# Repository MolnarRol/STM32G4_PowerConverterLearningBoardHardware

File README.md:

# STM32F4_PowerConverterLearningBoardHardware

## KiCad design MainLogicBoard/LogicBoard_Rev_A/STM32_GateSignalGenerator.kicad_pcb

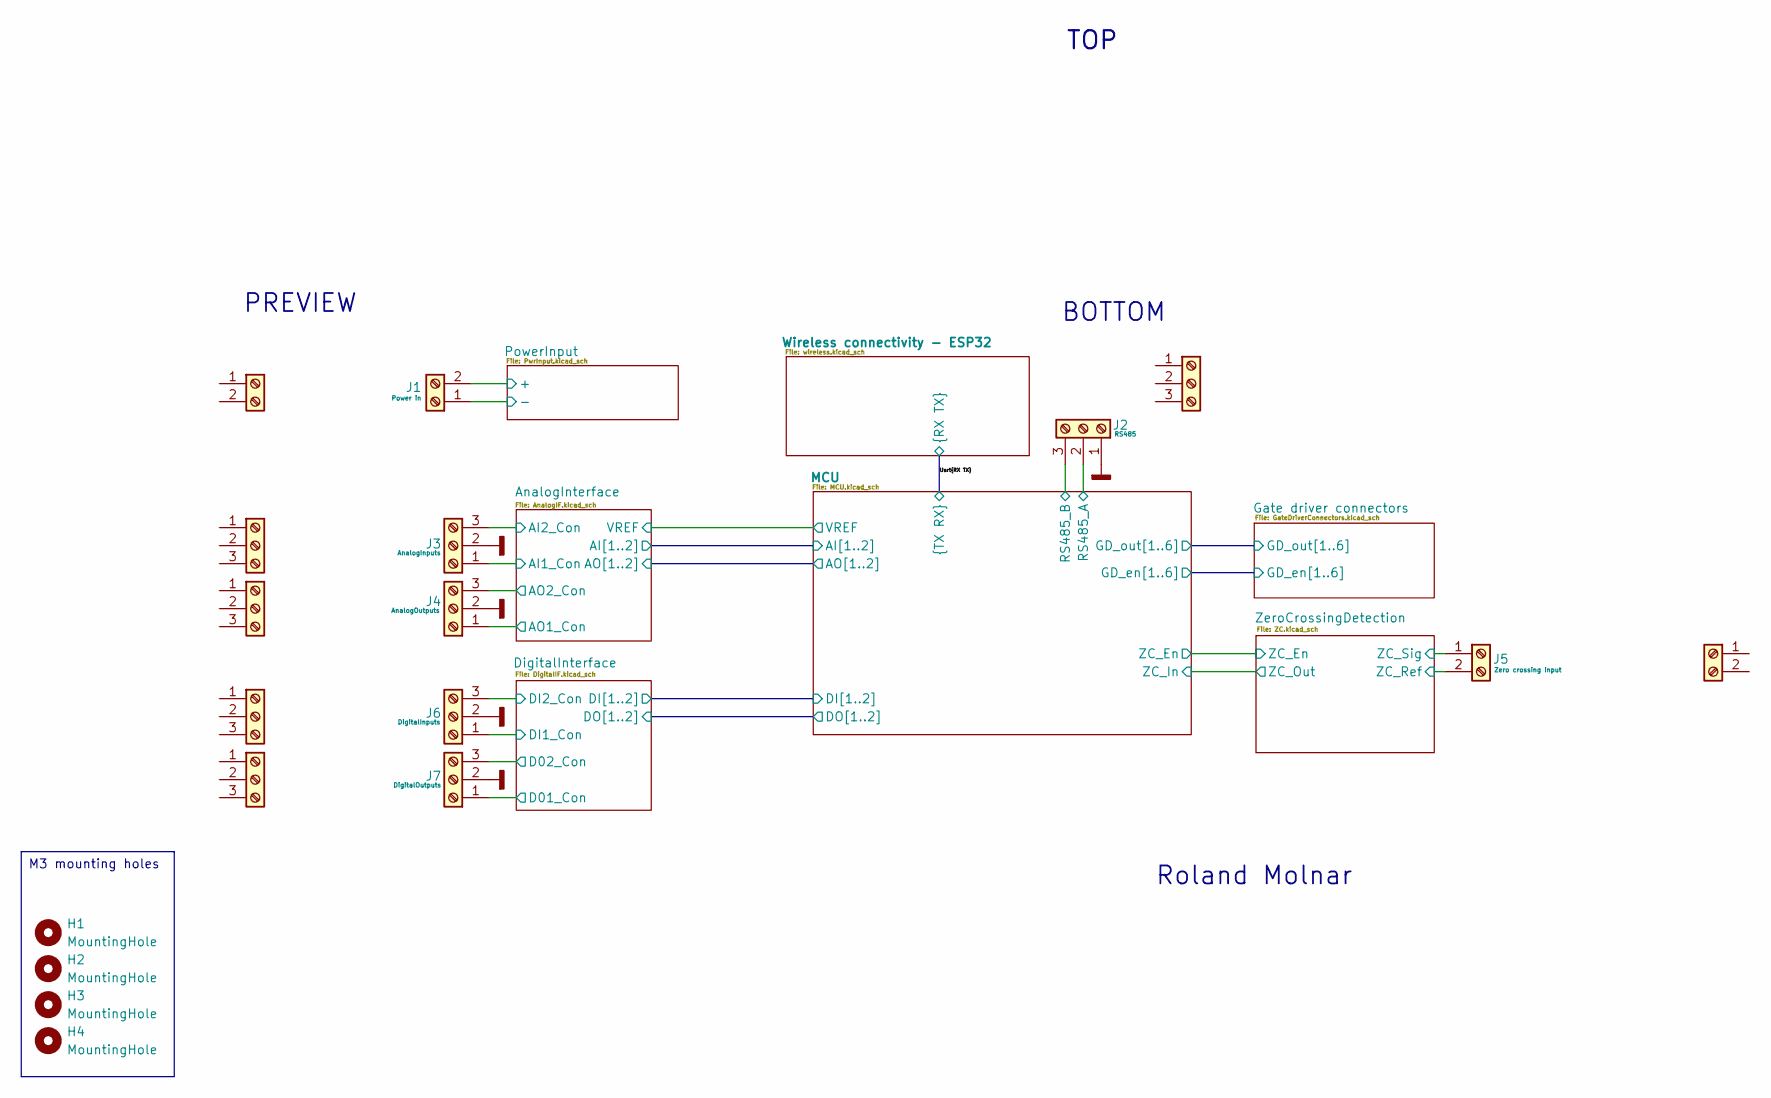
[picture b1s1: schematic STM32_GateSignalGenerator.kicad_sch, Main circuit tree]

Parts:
H1, H2, H3, H4: MountingHole; MountingHole_3.2mm_M3
J1: Power in; TE 2350514-2; Manufacturer PN 2350514-2; DigiKey PN A145378-ND
J2: RS485; TE 2350514-3; Manufacturer PN 2350514-3; DigiKey PN A145379-ND
J3: AnalogInputs; TE 2350514-3; Manufacturer PN 2350514-3; DigiKey PN A145379-ND
J4: AnalogOutputs; TE 2350514-3; Manufacturer PN 2350514-3; DigiKey PN A145379-ND
J5: Zero crossing input; PhoenixContact_MSTBA_2,5_2-G-5,08_1x02_P5.08mm_Horizontal; Manufacturer PN 1757242; DigiKey PN 277-1106-ND
J6: DigitalInputs; TE 2350514-3; Manufacturer PN 2350514-3; DigiKey PN A145379-ND
J7: DigitalOutputs; TE 2350514-3; Manufacturer PN 2350514-3; DigiKey PN A145379-ND
J22: Screw_Terminal_01x02; Manufacturer PN 2350398-2; DigiKey PN A145367-ND
J23, J24, J25, J26, J27: Screw_Terminal_01x03; Manufacturer PN 284506-3; DigiKey PN A98374-ND
J28: Screw_Terminal_01x02; Manufacturer PN 1757019; DigiKey PN 277-1011-ND

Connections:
/AnalogInterface/AI1_Con: J3.1; also elsewhere on the board
/AnalogInterface/AI2_Con: J3.3; also elsewhere on the board
/AnalogInterface/AO1_Con: J4.1; also elsewhere on the board
/AnalogInterface/AO2_Con: J4.3; also elsewhere on the board
/DigitalInterface/D01_Con: J7.1; also elsewhere on the board
/DigitalInterface/D02_Con: J7.3; also elsewhere on the board
/DigitalInterface/DI1_Con: J6.1; also elsewhere on the board
/DigitalInterface/DI2_Con: J6.3; also elsewhere on the board
/MCU/rs485_a: J2.2; also elsewhere on the board
/MCU/rs485_b: J2.3; also elsewhere on the board
/PowerInput/PWR_IN_+24V: J1.2; also elsewhere on the board
/ZeroCrossingDetection/ZC_Ref: J5.2; also elsewhere on the board
/ZeroCrossingDetection/ZC_Sig: J5.1; also elsewhere on the board
GNDD: J1.1, J2.1, J3.2, J4.2, J6.2, J7.2; also elsewhere on the board

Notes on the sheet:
PREVIEW
Roland Molnar
BOTTOM
TOP
M3 mounting holes

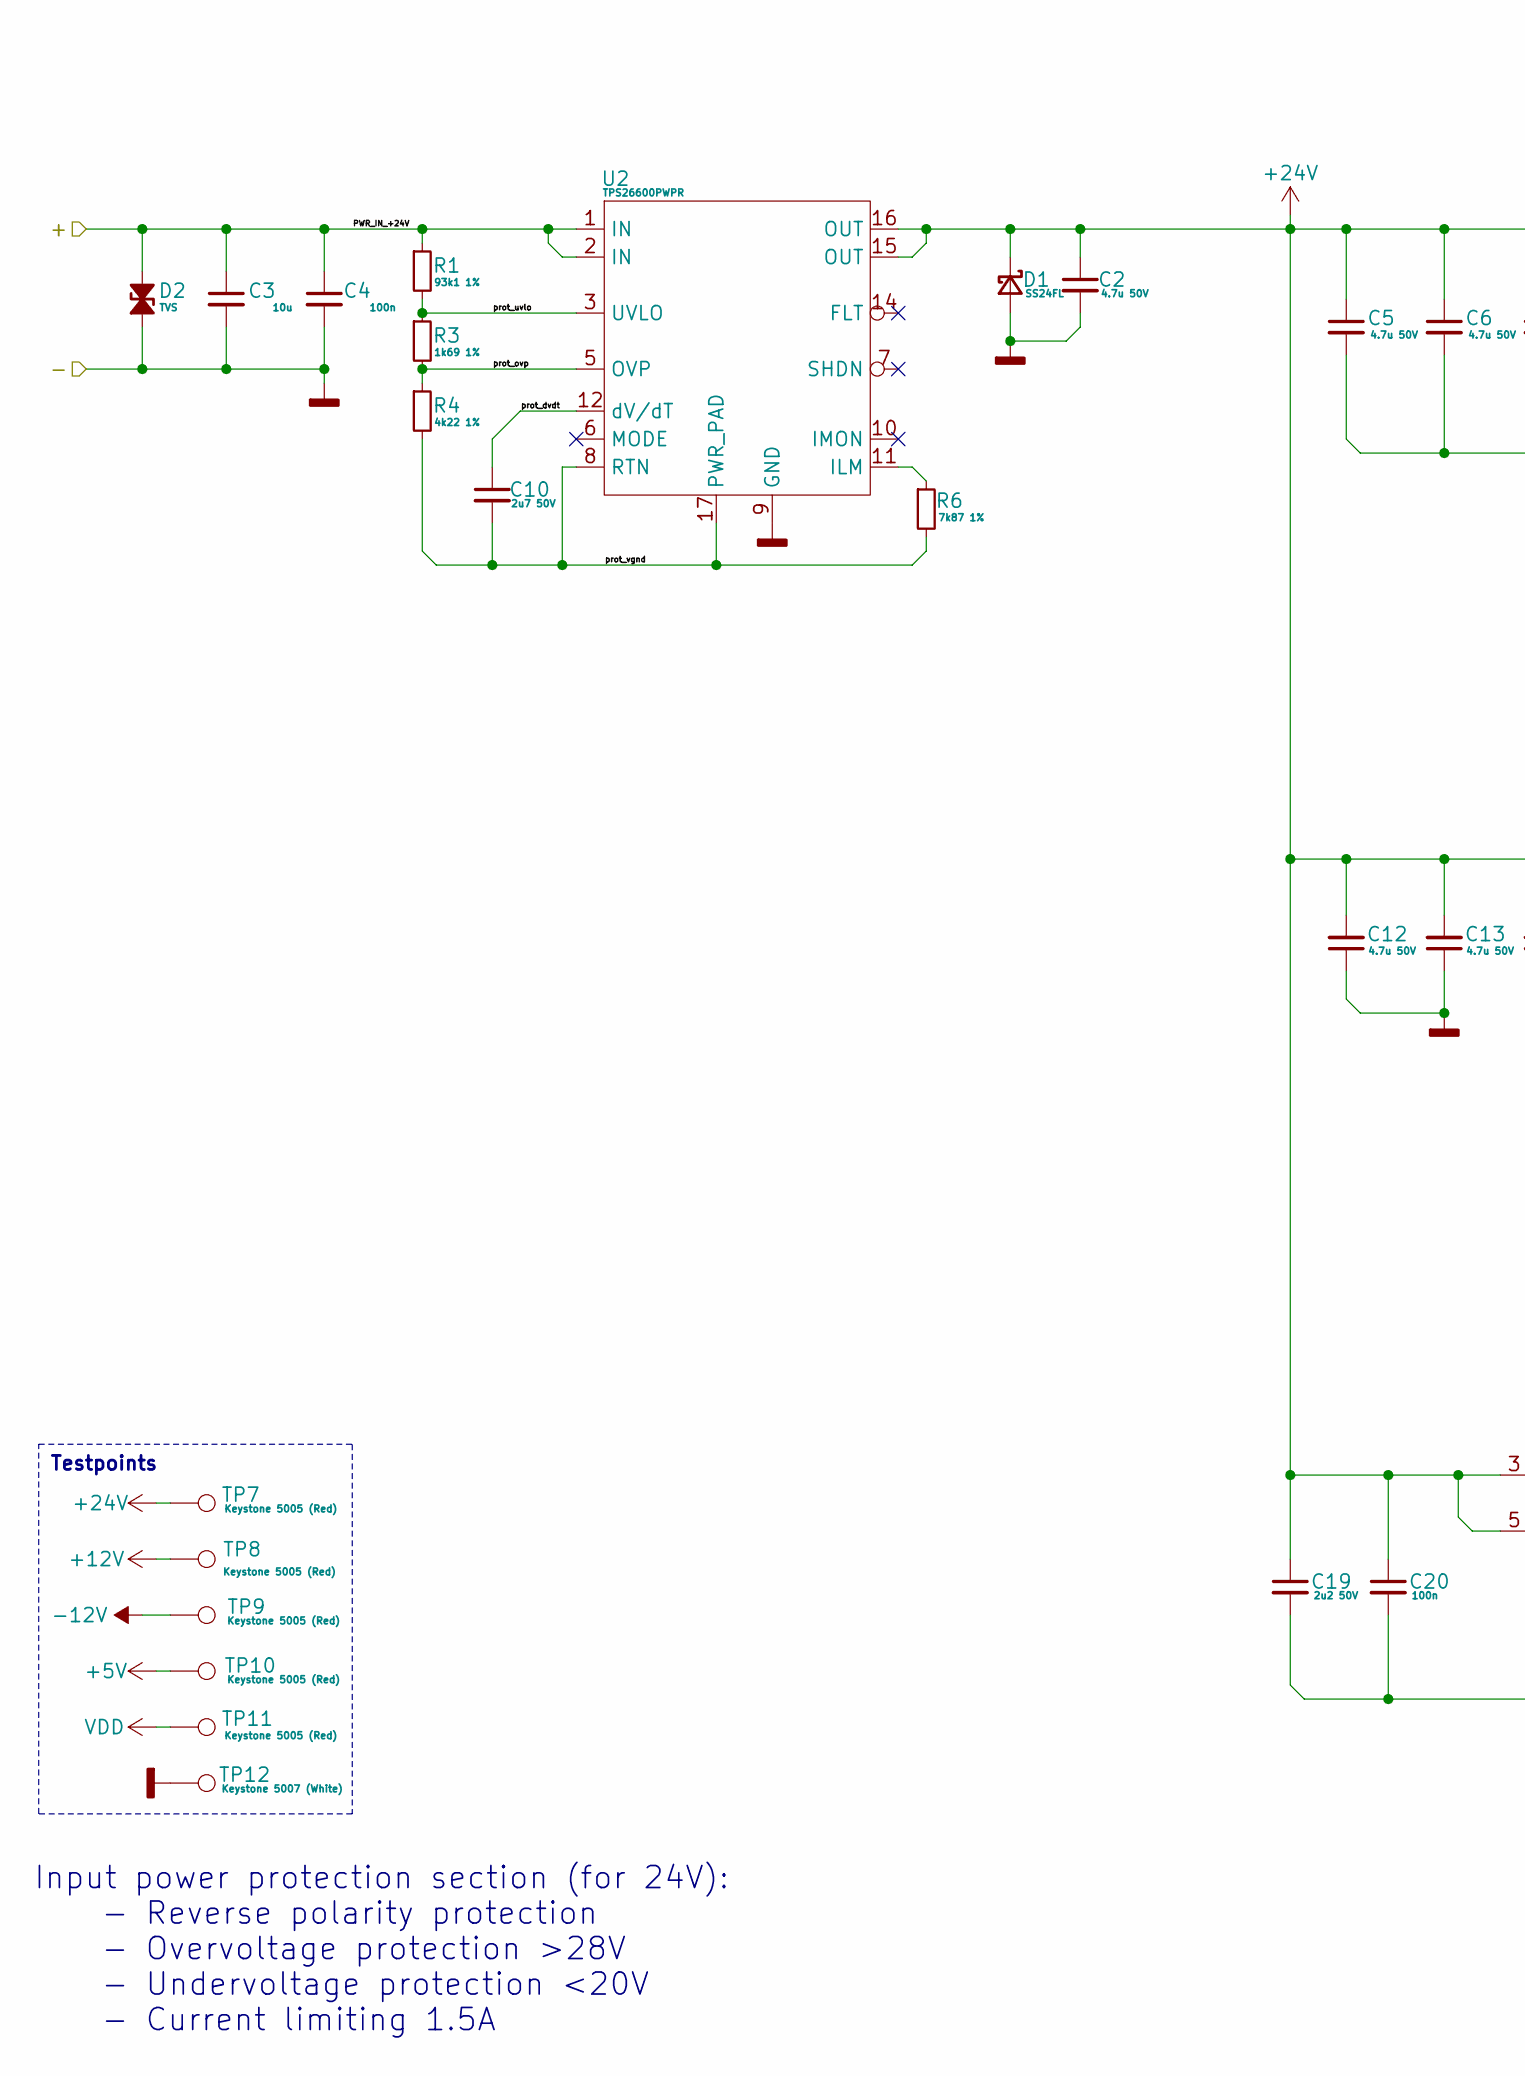
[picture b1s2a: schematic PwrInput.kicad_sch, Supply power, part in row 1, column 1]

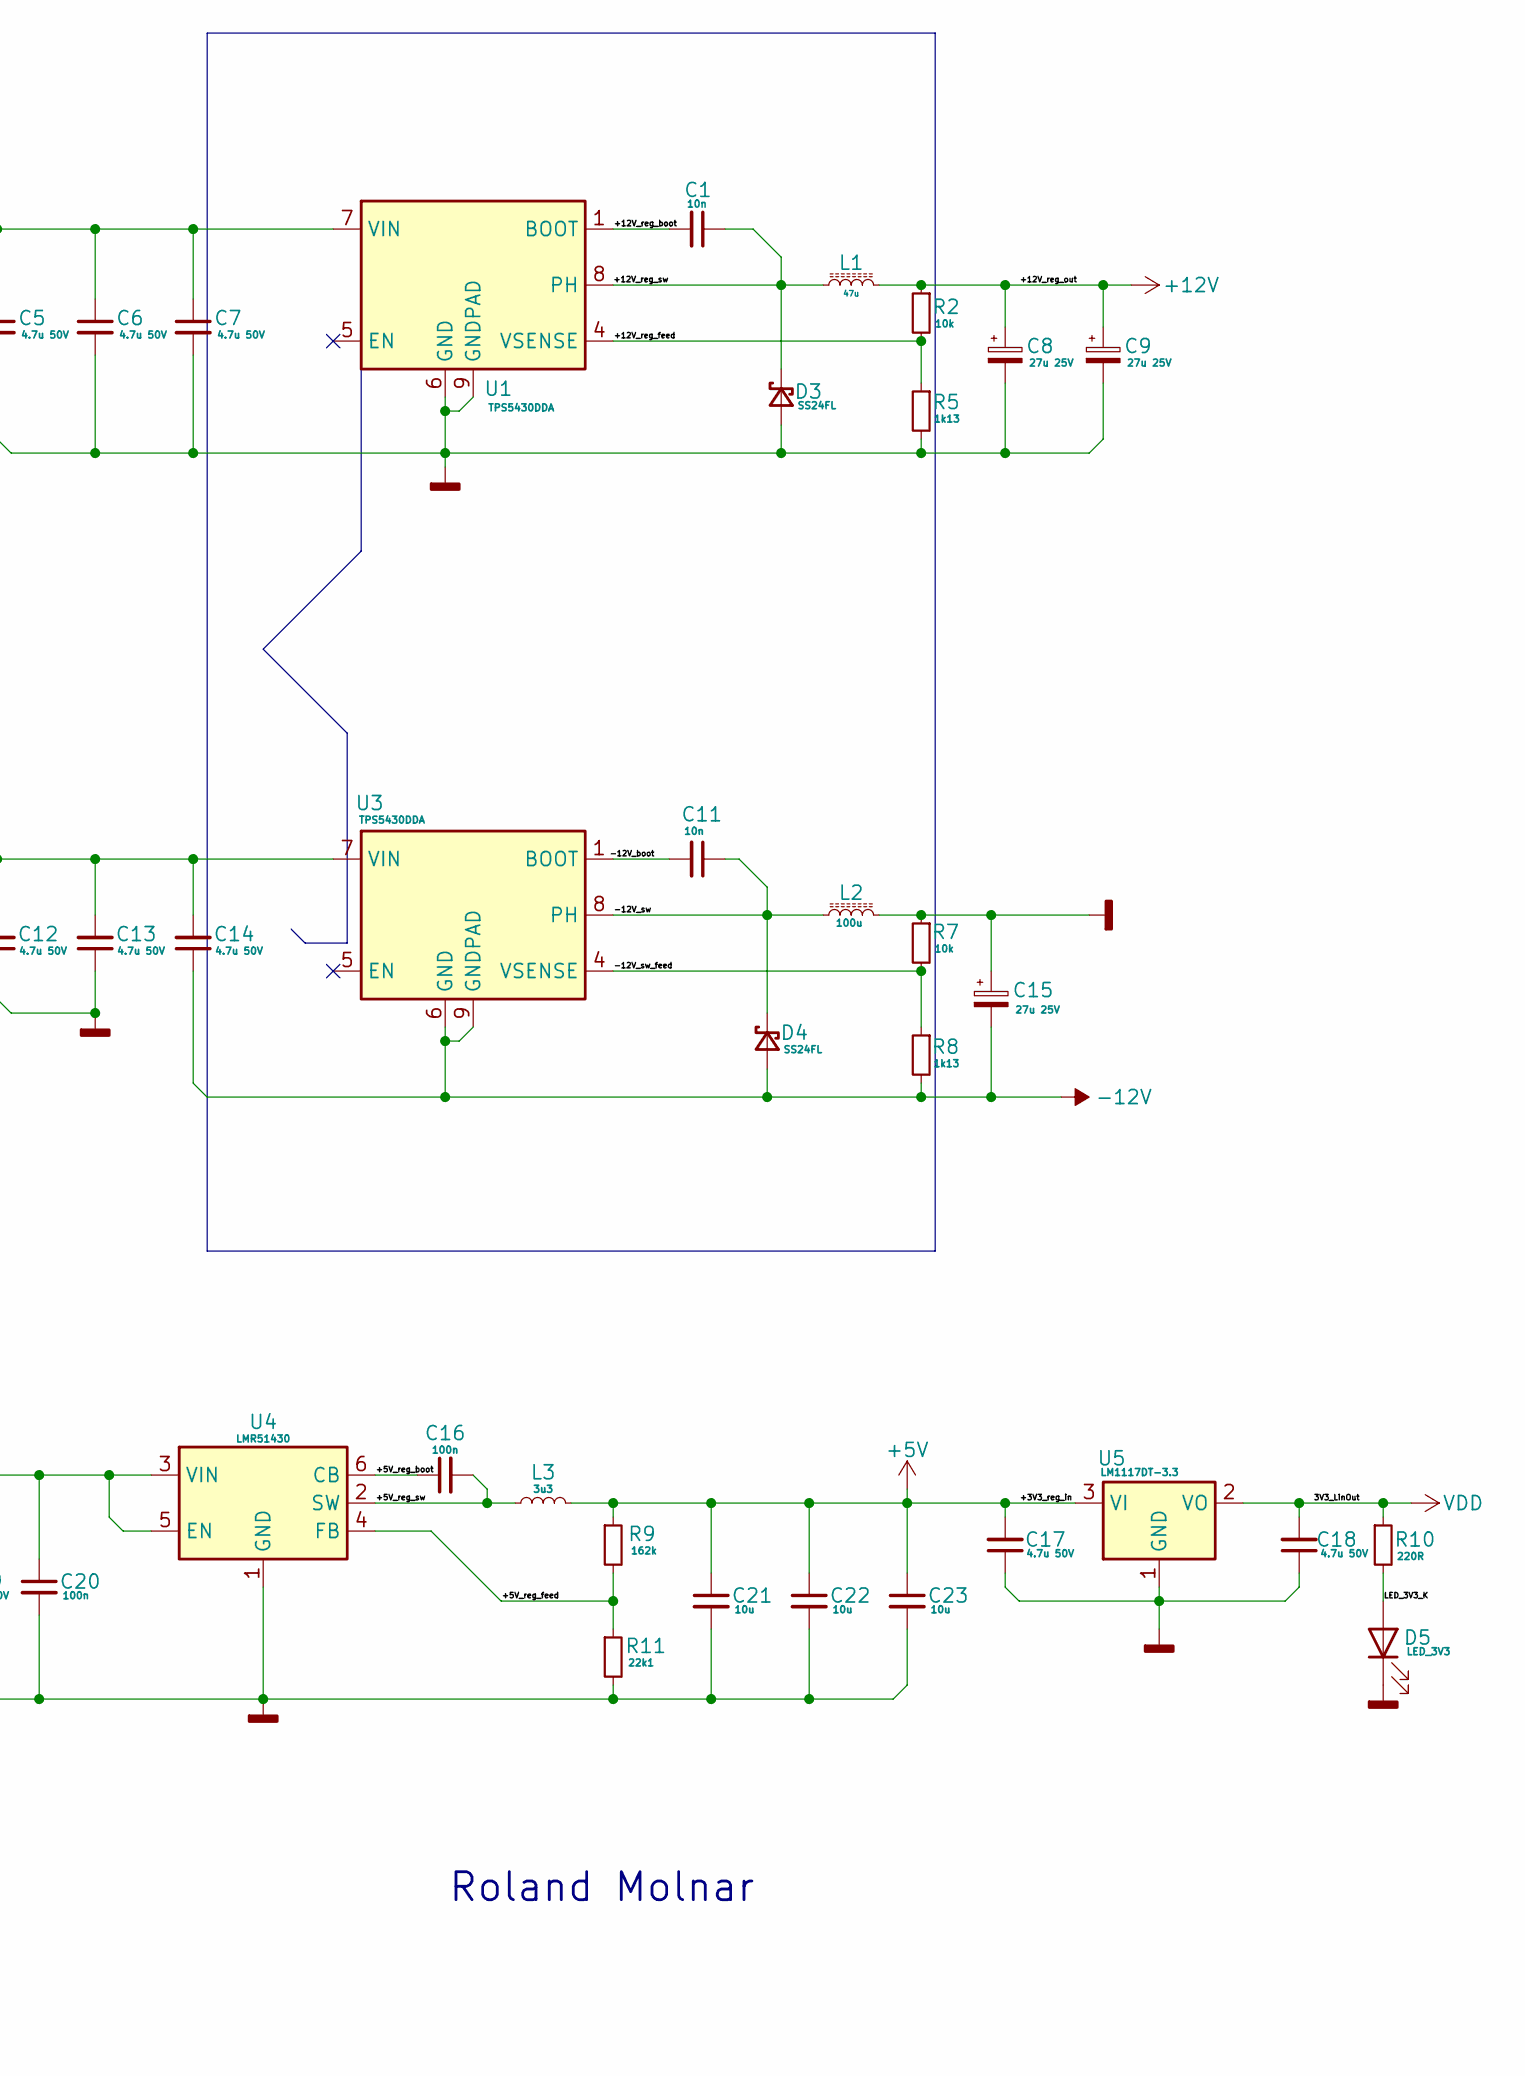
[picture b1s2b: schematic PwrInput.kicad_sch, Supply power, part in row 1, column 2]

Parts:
C1, C11: 10n; C_0805_2012Metric; Manufacturer PN KGM21NR71H103KT; DigiKey PN 478-KGM21NR71H103KTCT-ND
C2, C5, C6, C7, C12, C13, C14, C17, C18: 4.7u 50V; C_1206_3216Metric; Manufacturer PN GRM31CR71H475KA12L; DigiKey PN 490-6521-1-ND
C3, C21, C22, C23: 10u; C_0805_2012Metric; Manufacturer PN C0805C106K8PACTU; DigiKey PN 399-C0805C106K8PACTUCT-ND
C4: 100n; C_0805_2012Metric; Manufacturer PN C0805C104K5RAC7411; DigiKey PN 399-C0805C104K5RAC7210CT-ND
C8, C9, C15: 27u 25V; CP_Elec_6.3x5.8; Manufacturer PN UUD1E270MCL1GS; DigiKey PN 493-2271-1-ND
C10: 2u7 50V; C_0805_2012Metric; Manufacturer PN CL21A225KB9LNNC; DigiKey PN 1276-2409-1-ND
C16, C20: 100n; C_0603_1608Metric; Manufacturer PN 06035C104JAT2A; DigiKey PN 478-KGM15BR71H104JTCT-ND
C19: 2u2 50V; C_1206_3216Metric; Manufacturer PN 12065C225K4T2A; DigiKey PN 478-KAM31GR71H225KUCT-ND
D1, D3, D4: SS24FL; D_SOD-123F; Manufacturer PN SS24FL; DigiKey PN SS24FLCT-ND
D2: TVS; D_SOD-323; Manufacturer PN DESD1LIN2WSQ-7; DigiKey PN DESD1LIN2WSQ-7DICT-ND
D5: LED_3V3; LED_0805_2012Metric; Manufacturer PN LTST-C171KRKT; DigiKey PN 160-1427-1-ND
L1: 47u; L_Bourns_SRR1208_12.7x12.7mm; Manufacturer PN SRR1208-470YL; DigiKey PN SRR1208-470YLCT-ND
L2: 100u; L_Bourns-SRN8040_8x8.15mm; Manufacturer PN SDR0805-101KL; DigiKey PN 118-SDR0805-101KLCT-ND
L3: 3u3; L_Vishay_IHLP-4040; Manufacturer PN IHLP4040DZER3R3M01; DigiKey PN 541-1298-1-ND
R1: 93k1 1%; R_0805_2012Metric; Manufacturer PN RC0805FR-0793K1L; DigiKey PN 311-93.1KCRCT-ND
R2, R7: 10k; R_0805_2012Metric; Manufacturer PN RT0805DRD0710KL; DigiKey PN 311-2699-1-ND
R3: 1k69 1%; R_0805_2012Metric; Manufacturer PN RC0805FR-071K69L; DigiKey PN 311-1.69KCRCT-ND
R4: 4k22 1%; R_0805_2012Metric; Manufacturer PN RC0805FR-074K22L; DigiKey PN 311-4.22KCRCT-ND
R5, R8: 1k13; R_0805_2012Metric; Manufacturer PN RC0805FR-071K13L; DigiKey PN 311-1.13KCRCT-ND
R6: 7k87 1%; R_0805_2012Metric; Manufacturer PN RC0805FR-077K87L; DigiKey PN 311-7.87KCRCT-ND
R9: 162k; R_0805_2012Metric; Manufacturer PN RC0805FR-07162KL; DigiKey PN 311-162KCRCT-ND
R10: 220R; R_0805_2012Metric; Manufacturer PN RC0805FR-07220RL; DigiKey PN 311-220CRCT-ND
R11: 22k1; R_0805_2012Metric; Manufacturer PN RC0805FR-0722K1L; DigiKey PN 311-22.1KCRCT-ND
TP7, TP8, TP9, TP10, TP11: Keystone 5005 (Red); TestPoint_Keystone_5005-5009_Compact; Manufacturer PN 5005; DigiKey PN 36-5005-ND
TP12: Keystone 5007 (White); TestPoint_Keystone_5005-5009_Compact; Manufacturer PN 5007; DigiKey PN 36-5007-ND
U1, U3: TPS5430DDA; TI_SO-PowerPAD-8_ThermalVias; Manufacturer PN TPS5430DDA; DigiKey PN 296-19447-5-ND
U2: TPS26600PWPR; HTSSOP-16-1EP_4.4x5mm_P0.65mm_EP3.4x5mm_Mask3x3mm_ThermalVi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; Manufacturer PN TPS26600PWPR; DigiKey PN 296-47292-1-ND
U4: LMR51430; SOT-23-6; Manufacturer PN LMR51430YDDCR; DigiKey PN 296-LMR51430YDDCRCT-ND
U5: LM1117DT-3.3; TO-252-3_TabPin2; Manufacturer PN LM1117DT-3.3/NOPB; DigiKey PN LM1117DT-3.3/NOPB-ND

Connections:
+5V: C17.2, C21.1, C22.1, C23.1, L3.2, R9.1, TP10.1, U5.3 (VI)
+12V: C8.1, C9.1, L1.2, R2.1, TP8.1; also elsewhere on the board
+24V: C2.1, C5.1, C6.1, C7.1, C12.2, C13.2, C14.2, C19.1, C20.1, D1.1 (K), TP7.1, U1.5 (EN), U1.7 (VIN), U2.15 (OUT), U2.16 (OUT), U3.5 (EN), U3.7 (VIN), U4.3 (VIN), U4.5 (EN); also elsewhere on the board
-12V: C14.1, C15.2, D4.2 (A), R8.2, TP9.1, U3.6 (GND), U3.9 (GNDPAD); also elsewhere on the board
/PowerInput/+5V_reg_boot: C16.1, U4.6 (CB)
/PowerInput/+5V_reg_feed: R9.2, R11.1, U4.4 (FB)
/PowerInput/+5V_reg_sw: C16.2, L3.1, U4.2 (SW)
/PowerInput/+12V_reg_boot: C1.2, U1.1 (BOOT)
/PowerInput/+12V_reg_feed: R2.2, R5.1, U1.4 (VSENSE)
/PowerInput/+12V_reg_sw: C1.1, D3.1 (K), L1.1, U1.8 (PH)
/PowerInput/-12V_boot: C11.2, U3.1 (BOOT)
/PowerInput/-12V_sw: C11.1, D4.1 (K), L2.1, U3.8 (PH)
/PowerInput/-12V_sw_feed: R7.2, R8.1, U3.4 (VSENSE)
/PowerInput/LED_3V3_K: D5.2 (A), R10.2
/PowerInput/PWR_IN_+24V: C3.1, C4.1, D2.2 (A2), R1.1, U2.1 (IN), U2.2 (IN); also elsewhere on the board
/PowerInput/prot_dvdt: C10.1, U2.12 (dV/dT)
/PowerInput/prot_ovp: R3.2, R4.1, U2.5 (OVP)
/PowerInput/prot_uvlo: R1.2, R3.1, U2.3 (UVLO)
/PowerInput/prot_vgnd: C10.2, R4.2, R6.2, U2.8 (RTN), U2.17 (PWR_PAD)
GNDD: C2.2, C3.2, C4.2, C5.2, C6.2, C7.2, C8.2, C9.2, C12.1, C13.1, C15.1, C17.1, C18.1, C19.2, C20.2, C21.2, C22.2, C23.2, D1.2 (A), D2.1 (A1), D3.2 (A), D5.1 (K), L2.2, R5.2, R7.1, R11.2, TP12.1, U1.6 (GND), U1.9 (GNDPAD), U2.9 (GND), U4.1 (GND), U5.1 (GND); also elsewhere on the board
unnamed: R6.1, U2.11 (ILM)
VDD: C18.2, R10.1, TP11.1, U5.2 (VO); also elsewhere on the board

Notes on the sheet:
Input power protection section (for 24V): - Reverse polarity protection - Overvoltage protection >28V - Undervoltage protection <20V - Current limiting 1.5A
Roland Molnar
Testpoints

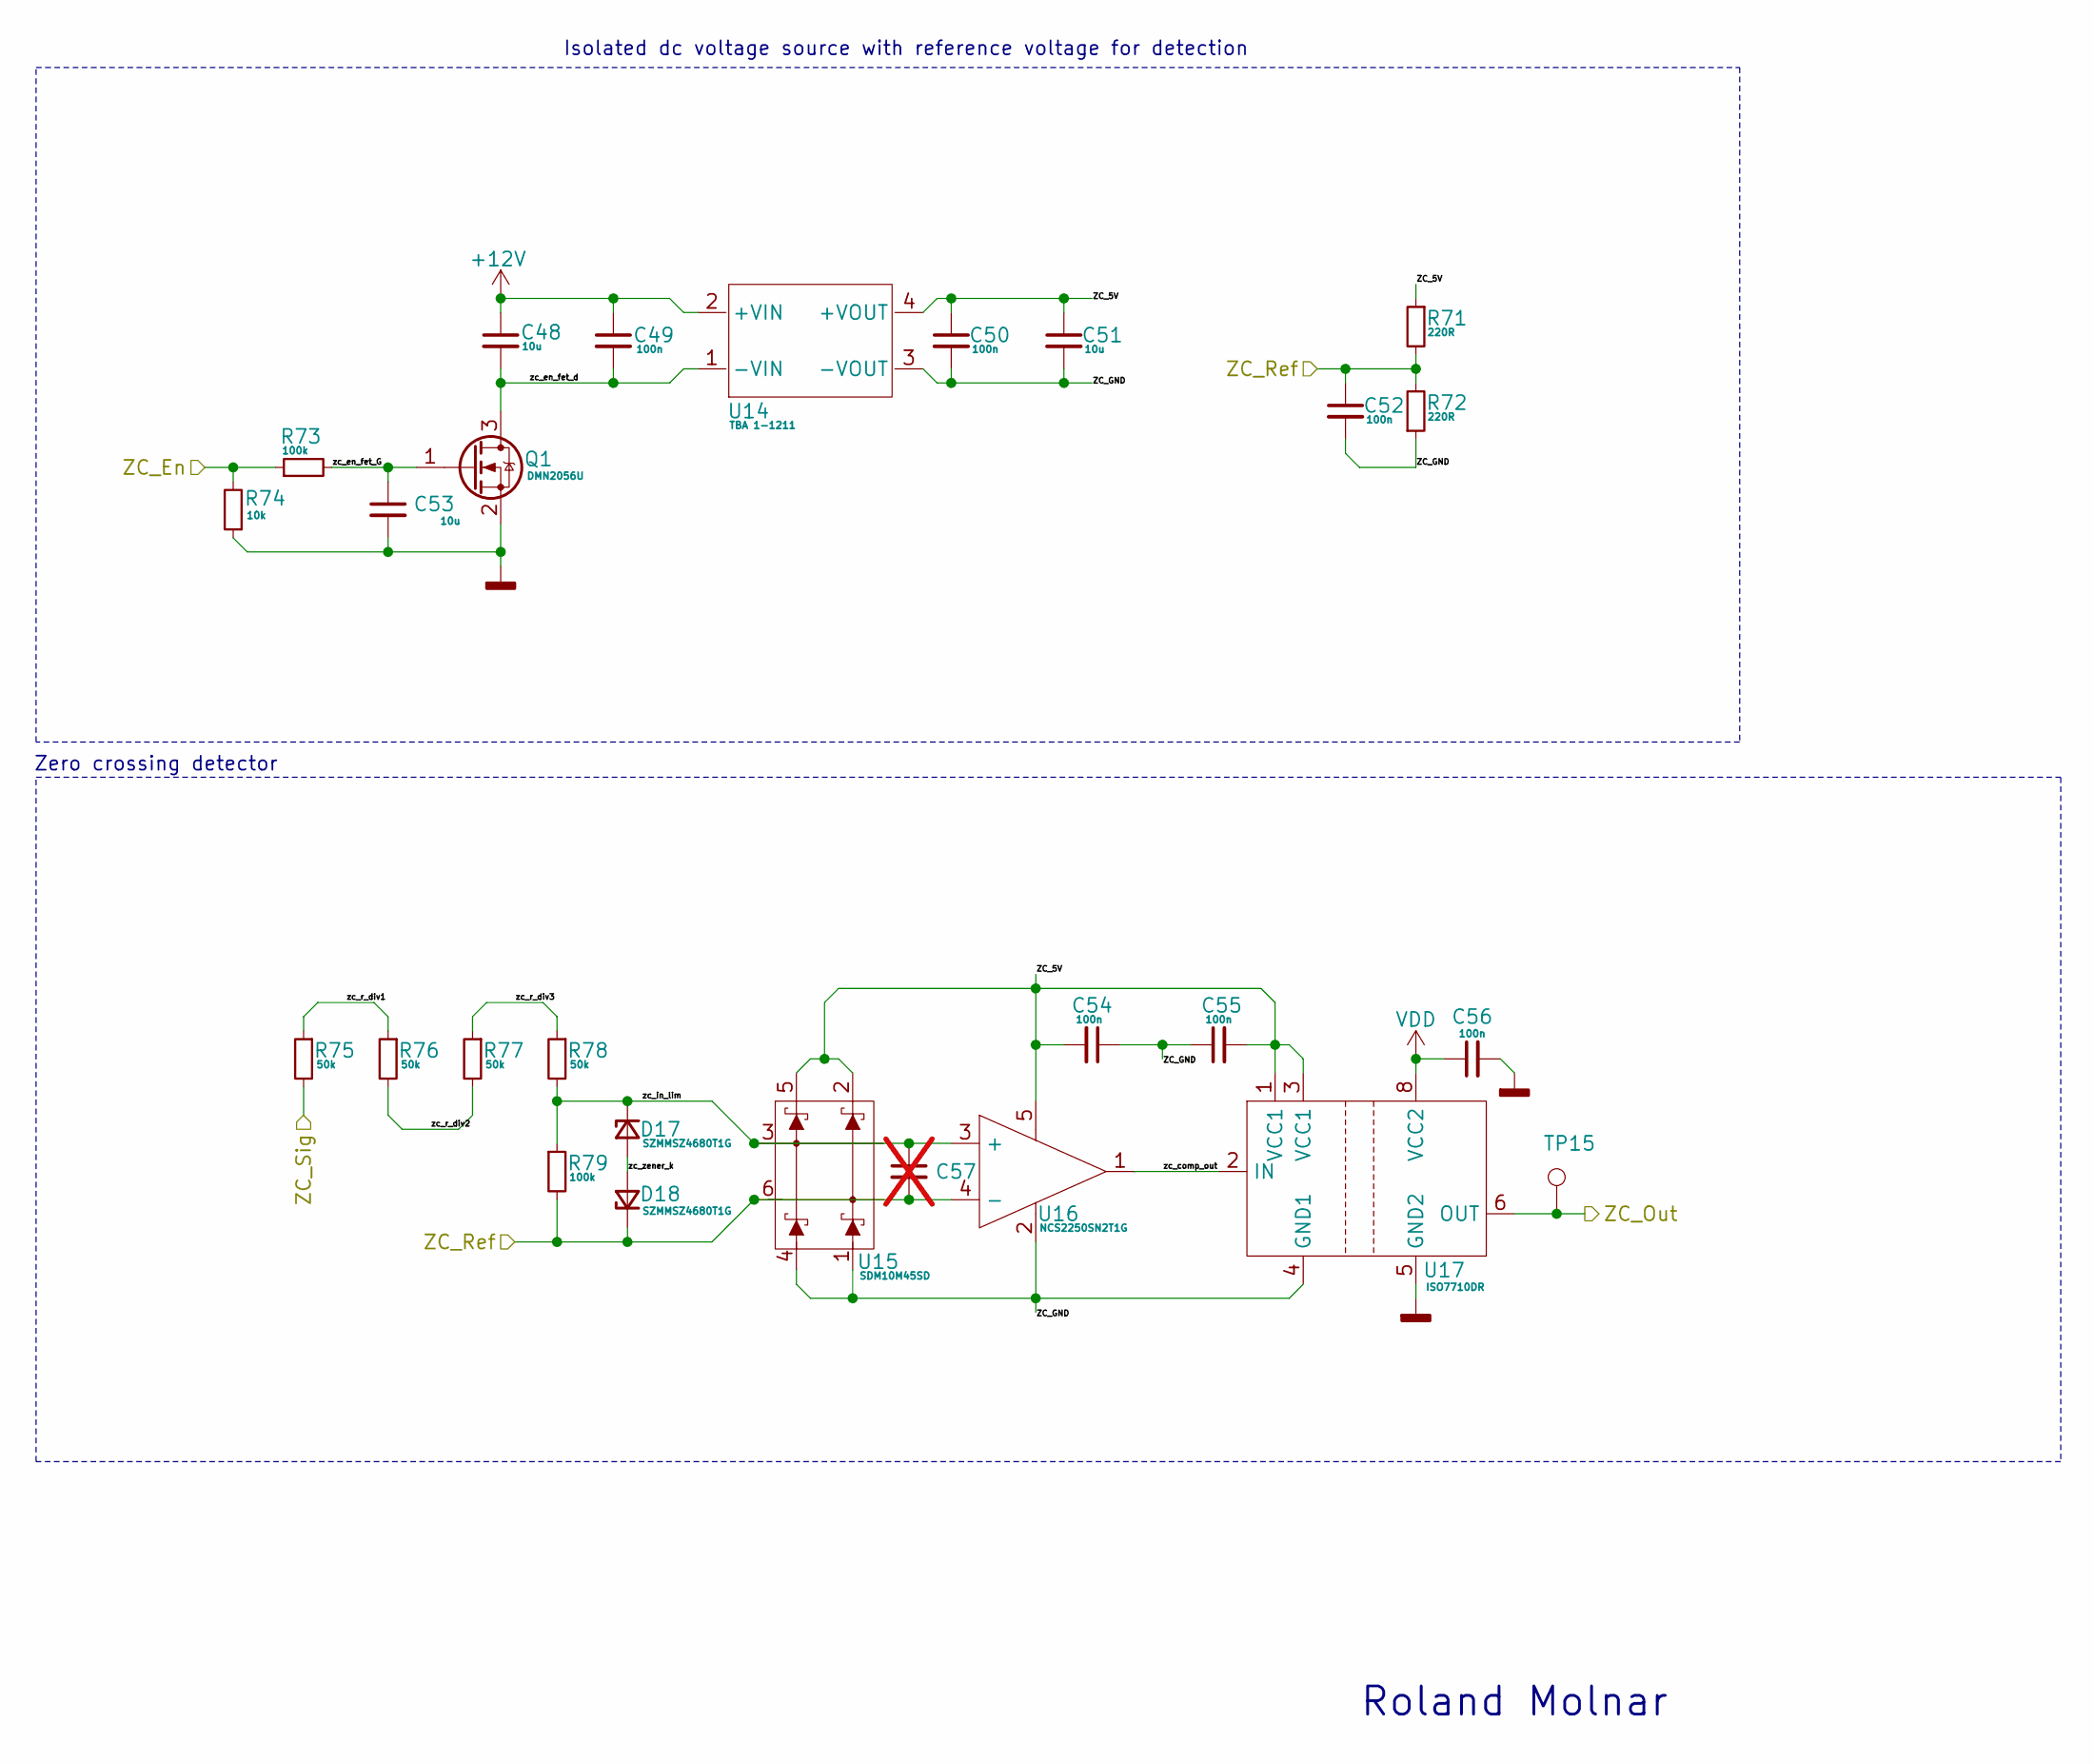
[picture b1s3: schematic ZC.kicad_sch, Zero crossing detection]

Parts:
C48, C51, C53: 10u; C_0805_2012Metric; Manufacturer PN C0805C106K8PACTU; DigiKey PN 399-C0805C106K8PACTUCT-ND
C49, C50, C52, C54, C55, C56: 100n; C_0805_2012Metric; Manufacturer PN C0805C104K5RAC7411; DigiKey PN 399-C0805C104K5RAC7210CT-ND
C57: C_Small; C_0805_2012Metric; not fitted
D17, D18: SZMMSZ4680T1G; D_SOD-123; Manufacturer PN SZMMSZ4680T1G; DigiKey PN SZMMSZ4680T1GOSCT-ND
Q1: DMN2056U; SOT-23; Manufacturer PN DMN2056U-7; DigiKey PN DMN2056U-7DICT-ND
R71, R72: 220R; R_1206_3216Metric; Manufacturer PN RT1206BRD07220RL; DigiKey PN YAG5046CT-ND
R73, R79: 100k; R_0805_2012Metric; Manufacturer PN RC0805FR-07100KL; DigiKey PN 311-100KCRCT-ND
R74: 10k; R_0805_2012Metric; Manufacturer PN RT0805DRD0710KL; DigiKey PN 311-2699-1-ND
R75, R76, R77, R78: 50k; R_2010_5025Metric; Manufacturer PN CRCW201049K9FKEF; DigiKey PN 541-49.9KACCT-ND
TP15: Keystone 5009 (Yellow); TestPoint_Keystone_5005-5009_Compact; Manufacturer PN 5009; DigiKey PN 36-5009-ND
U14: TBA 1-1211; Manufacturer PN TBA 1-1211; DigiKey PN 1951-3373-ND
U15: SDM10M45SD; Manufacturer PN SDM10M45SD-7-F; DigiKey PN SDM10M45SD-FDICT-ND
U16: NCS2250SN2T1G; SOT-23-5; Manufacturer PN NCS2250SN2T1G; DigiKey PN NCS2250SN2T1GOSCT-ND
U17: ISO7710DR; SOIC-8_3.9x4.9mm_P1.27mm; Manufacturer PN ISO7710DR; DigiKey PN 296-48557-1-ND

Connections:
+12V: C48.1, C49.1, U14.2 (+VIN); also elsewhere on the board
/MCU/ZC_En: R73.1, R74.2; also elsewhere on the board
/MCU/ZC_In: TP15.1, U17.6 (OUT); also elsewhere on the board
/ZeroCrossingDetection/ZC_5V: C50.1, C51.1, C54.2, C55.2, R71.1, U14.4 (+VOUT), U15.2, U15.5, U16.5, U17.1 (VCC1), U17.3 (VCC1)
/ZeroCrossingDetection/ZC_GND: C50.2, C51.2, C52.2, C54.1, C55.1, R72.1, U14.3 (-VOUT), U15.1, U15.4, U16.2, U17.4 (GND1)
/ZeroCrossingDetection/ZC_Ref: C52.1, C57.2, D18.1 (K), R71.2, R72.2, R79.2, U15.6, U16.4 (-); also elsewhere on the board
/ZeroCrossingDetection/ZC_Sig: R75.2; also elsewhere on the board
/ZeroCrossingDetection/zc_comp_out: U16.1, U17.2 (IN)
/ZeroCrossingDetection/zc_en_fet_G: C53.1, Q1.1 (G), R73.2
/ZeroCrossingDetection/zc_en_fet_d: C48.2, C49.2, Q1.3 (D), U14.1 (-VIN)
/ZeroCrossingDetection/zc_in_lim: C57.1, D17.1 (K), R78.2, R79.1, U15.3, U16.3 (+)
/ZeroCrossingDetection/zc_r_div1: R75.1, R76.1
/ZeroCrossingDetection/zc_r_div2: R76.2, R77.2
/ZeroCrossingDetection/zc_r_div3: R77.1, R78.1
/ZeroCrossingDetection/zc_zener_k: D17.2 (A), D18.2 (A)
GNDD: C53.2, C56.2, Q1.2 (S), R74.1, U17.5 (GND2); also elsewhere on the board
VDD: C56.1, U17.8 (VCC2); also elsewhere on the board

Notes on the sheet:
Zero crossing detector
Isolated dc voltage source with reference voltage for detection
Roland Molnar
